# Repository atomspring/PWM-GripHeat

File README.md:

# PWM-GripHeat
Rugged PWM control for a grip heater using an attiny85 and a beefy NMOS, supporting a dual color or RGB indicator, with careful attention paid to power usage.

KiCad 8.0 Schematics and PCB files are (as expected) under the "hardware" folder, firmware is under the "firmware" folder.

Cost for a single board was TODO: fill in total costs, total including optional mechanical components was TODO:

## Hardware

The BOM (bill-of-materials) is relatively short, holding all mechanical components in [here](<hardware/bom/Mechanical BOM.md>), and the PCB components [here](<hardware/bom/BOM-PWM GripHeat-1.0.html>).

Assembly should take about an hour's work with the right tools. I use lead-free solder paste for all my work, with the PCB itself using ENIG for all pads. Soldering is sped up by using a hand-held hot air reflow gun, but all pads are big enough to facilitate hand soldering.

## Firmware
I'm using PlatformIO on VSCodium to write the fairly simple firmware, build steps:
1. Item 1
1. rr
1. te

## License
This project is:
- Software: GPL3 protected
- Hardware: CERN-OHL-S-2.0 (https://spdx.org/licenses/CERN-OHL-S-2.0.html)

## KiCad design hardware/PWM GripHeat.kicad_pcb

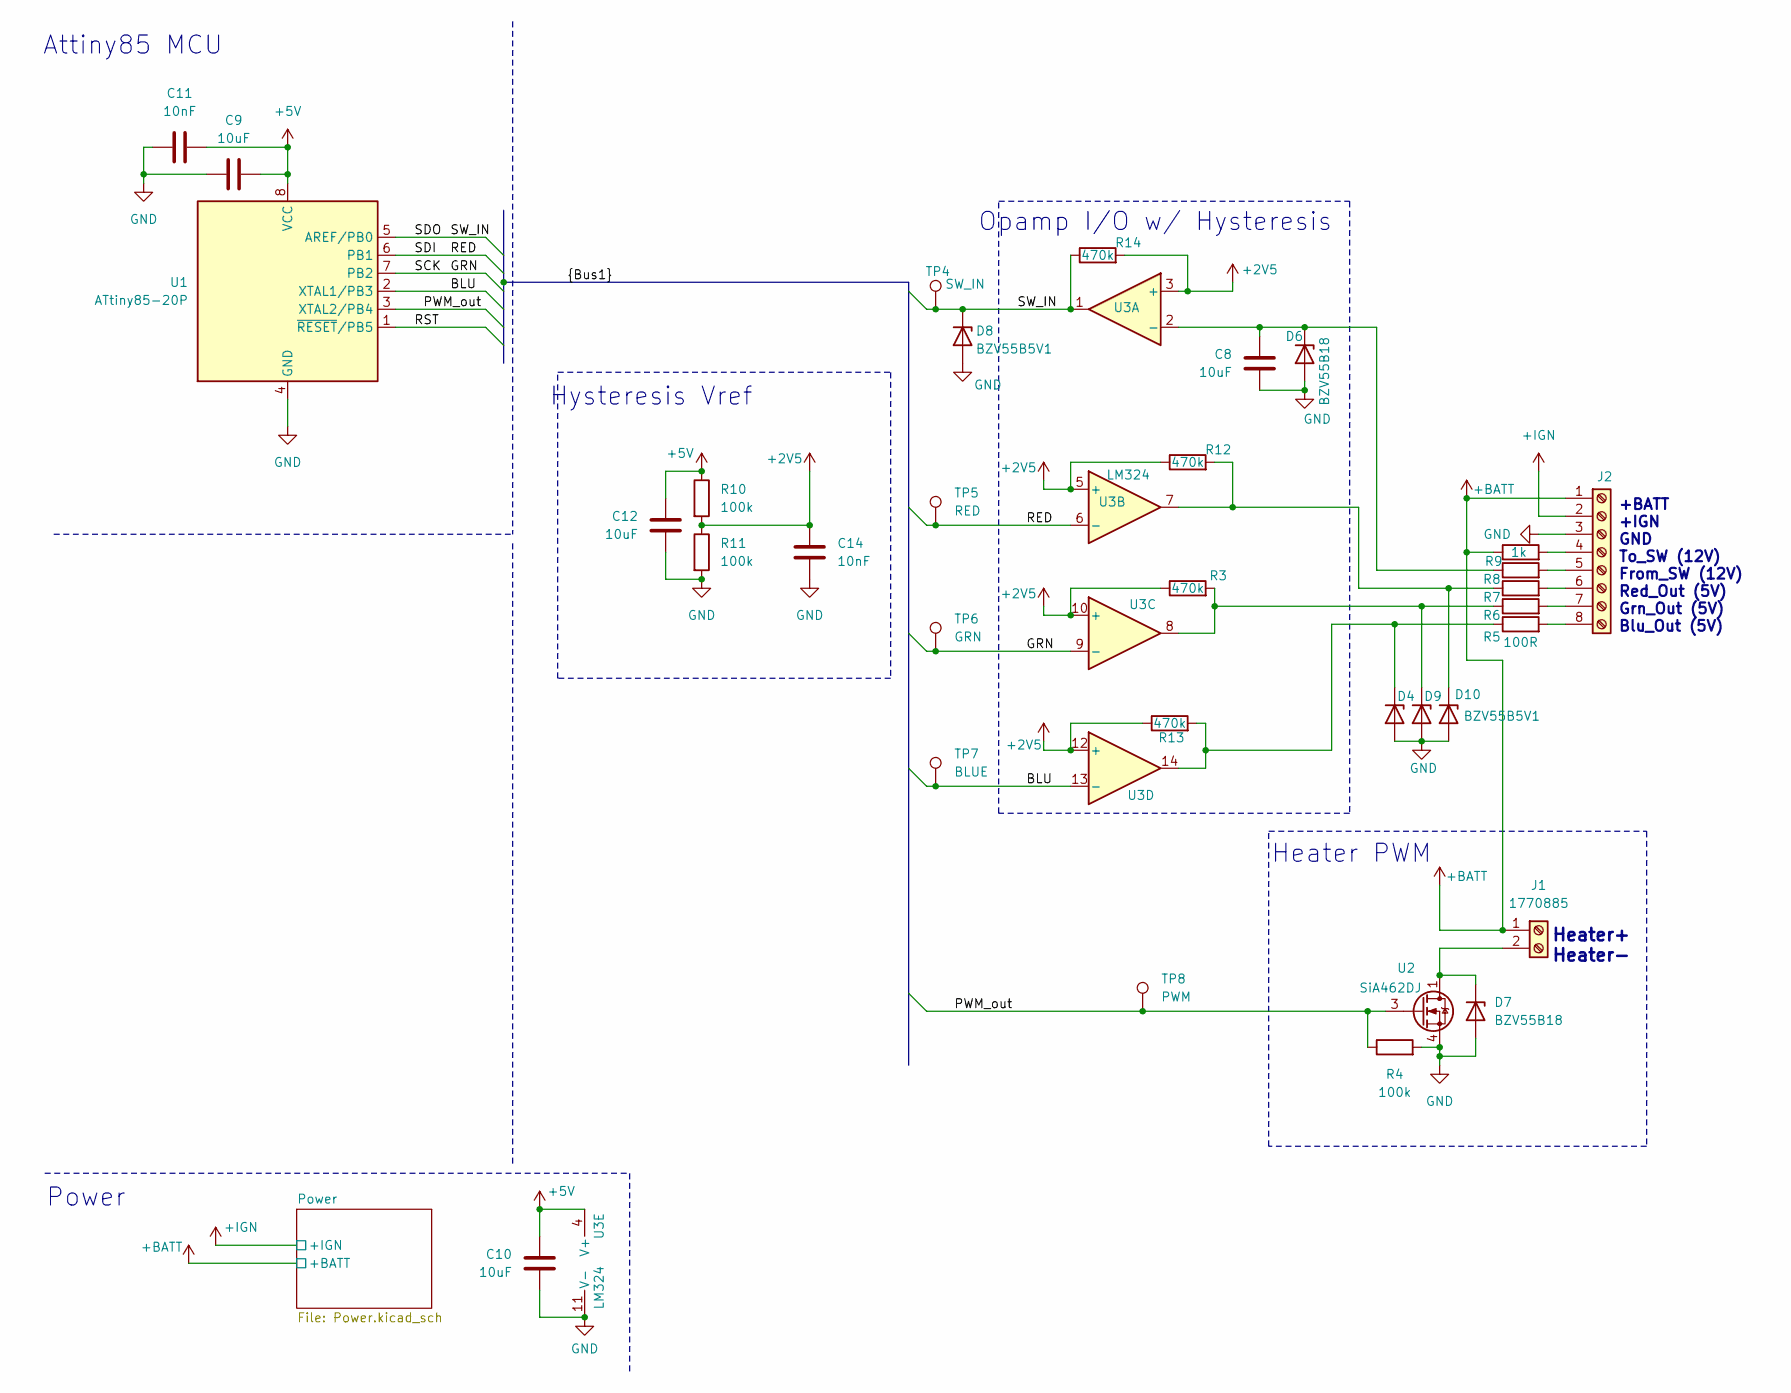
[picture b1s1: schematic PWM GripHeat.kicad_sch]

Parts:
C8, C9, C10, C12: 10uF; C_0805_2012Metric_Pad1.18x1.45mm_HandSolder; Voltage Rating 100v
C11, C14: 10nF; C_0805_2012Metric_Pad1.18x1.45mm_HandSolder
D4, D8, D9, D10: BZV55B5V1; D_MiniMELF
D6, D7: BZV55B18; D_MiniMELF
J1: 1770885; TerminalBlock_MaiXu_MX126-5.0-02P_1x02_P5.00mm
J2: Screw_Terminal_01x08; PinHeader_2x04_P2.54mm_Vertical
R3, R12, R13, R14: 470k; R_0805_2012Metric_Pad1.20x1.40mm_HandSolder
R4: 100k; R_1206_3216Metric_Pad1.30x1.75mm_HandSolder
R5, R6, R7, R8: 100R; R_0805_2012Metric_Pad1.20x1.40mm_HandSolder
R9: 1k; R_0805_2012Metric_Pad1.20x1.40mm_HandSolder
R10, R11: 100k; R_0805_2012Metric_Pad1.20x1.40mm_HandSolder
TP4: SW_IN; TestPoint_Pad_D1.5mm
TP5: RED; TestPoint_Pad_D1.5mm
TP6: GRN; TestPoint_Pad_D1.5mm
TP7: BLUE; TestPoint_Pad_D1.5mm
TP8: PWM; TestPoint_Pad_D1.5mm
U1: ATtiny85-20P; DIP-8_W7.62mm
U2: SiA462DJ; Vishay_PowerPAK_SC70-6L_Single
U3: LM324; SOIC-14_3.9x8.7mm_P1.27mm

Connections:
+2V5: C14.2, R3.1, R10.2, R11.1, R12.1, R13.1, R14.2, U3.3 (+), U3.5 (+), U3.10 (+), U3.12 (+)
+5V: C9.2, C10.2, C11.2, C12.2, R10.1, U1.8 (VCC), U3.4 (V+); also elsewhere on the board
+BATT: J1.1, J2.1, R9.1; also elsewhere on the board
+IGN: J2.2; also elsewhere on the board
/BLU: TP7.1, U1.2 (XTAL1/PB3), U3.13 (-)
/GRN: TP6.1, U1.7 (PB2), U3.9 (-)
/PWM_out: R4.1, TP8.1, U1.3 (XTAL2/PB4), U2.3 (G)
/RED: TP5.1, U1.6 (PB1), U3.6 (-)
/RST: U1.1 (~RESET/PB5)
/SDO: D8.1 (K), R14.1, TP4.1, U1.5 (AREF/PB0), U3.1
GND: C8.1, C9.1, C10.1, C11.1, C12.1, C14.1, D4.2 (A), D6.2 (A), D7.2 (A), D8.2 (A), D9.2 (A), D10.2 (A), J2.3, R4.2, R11.2, U1.4 (GND), U2.4 (S), U3.11 (V-); also elsewhere on the board
unnamed: D4.1 (K), R5.1, R13.2, U3.14
unnamed: C8.2, D6.1 (K), R8.1, U3.2 (-)
unnamed: D7.1 (K), J1.2, U2.1 (D)
unnamed: D9.1 (K), R3.2, R6.1, U3.8
unnamed: D10.1 (K), R7.1, R12.2, U3.7
unnamed: J2.4, R9.2
unnamed: J2.5, R8.2
unnamed: J2.6, R7.2
unnamed: J2.7, R6.2
unnamed: J2.8, R5.2

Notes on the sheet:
Hysteresis Vref
+BATT +IGN GND To_SW (12V) From_SW (12V) Red_Out (5V) Grn_Out (5V) Blu_Out (5V)
Heater PWM
Opamp I/O w/ Hysteresis
Heater+ Heater-
Attiny85 MCU
Power

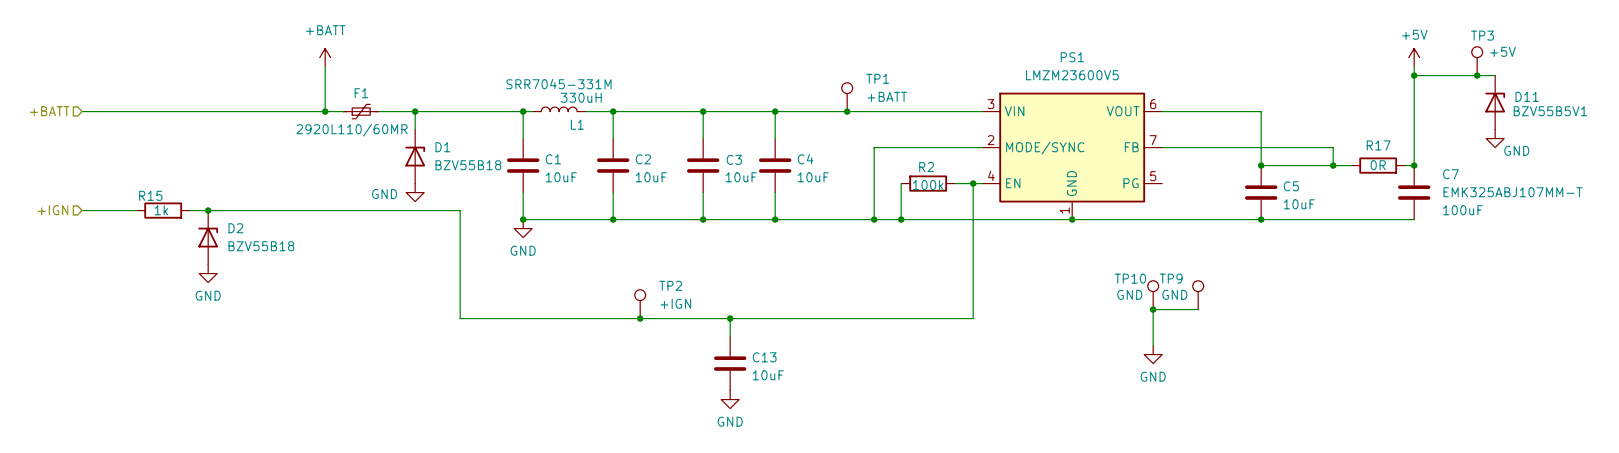
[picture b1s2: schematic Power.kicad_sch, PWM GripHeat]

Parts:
C1, C2, C3, C4, C5, C13: 10uF; C_0805_2012Metric_Pad1.18x1.45mm_HandSolder; Voltage Rating 100v
C7: EMK325ABJ107MM-T; C_1210_3225Metric_Pad1.33x2.70mm_HandSolder; Voltage Rating 16v
D1, D2: BZV55B18; D_MiniMELF
D11: BZV55B5V1; D_MiniMELF
F1: Polyfuse_Small; Fuse_2920_7451Metric_Pad2.10x5.45mm_HandSolder; MPN 2920L110/60MR
L1: 330uH; L_Bourns_SRR7045; MPN SRR7045-331M
PS1: LMZM23600V5; Texas_SIL0010A_MicroSiP-10-1EP_3.8x3mm_P0.6mm_EP0.7x2.9mm_T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
R2: 100k; R_1206_3216Metric_Pad1.30x1.75mm_HandSolder
R15: 1k; R_0805_2012Metric_Pad1.20x1.40mm_HandSolder
R17: 0R; R_0805_2012Metric_Pad1.20x1.40mm_HandSolder
TP1: +BATT; TestPoint_Pad_D1.5mm
TP2: +IGN; TestPoint_THTPad_D1.0mm_Drill0.5mm
TP3: +5V; TestPoint_Pad_D1.5mm
TP9, TP10: GND; TestPoint_THTPad_D2.0mm_Drill1.0mm

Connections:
+5V: C7.1, D11.1 (K), R17.2, TP3.1; also elsewhere on the board
+BATT: F1.1; also elsewhere on the board
+IGN: R15.1; also elsewhere on the board
GND: C1.2, C2.2, C3.2, C4.2, C5.2, C7.2, C13.2, D1.2 (A), D2.2 (A), D11.2 (A), PS1.1 (GND), PS1.2 (MODE/SYNC), PS1.11 (GND), R2.2, TP9.1, TP10.1; also elsewhere on the board
unnamed: C1.1, D1.1 (K), F1.2, L1.1
unnamed: C13.1, D2.1 (K), PS1.4 (EN), R2.1, R15.2, TP2.1
unnamed: C5.1, PS1.6 (VOUT), PS1.7 (FB), R17.1
unnamed: C2.1, C3.1, C4.1, L1.2, PS1.3 (VIN), TP1.1

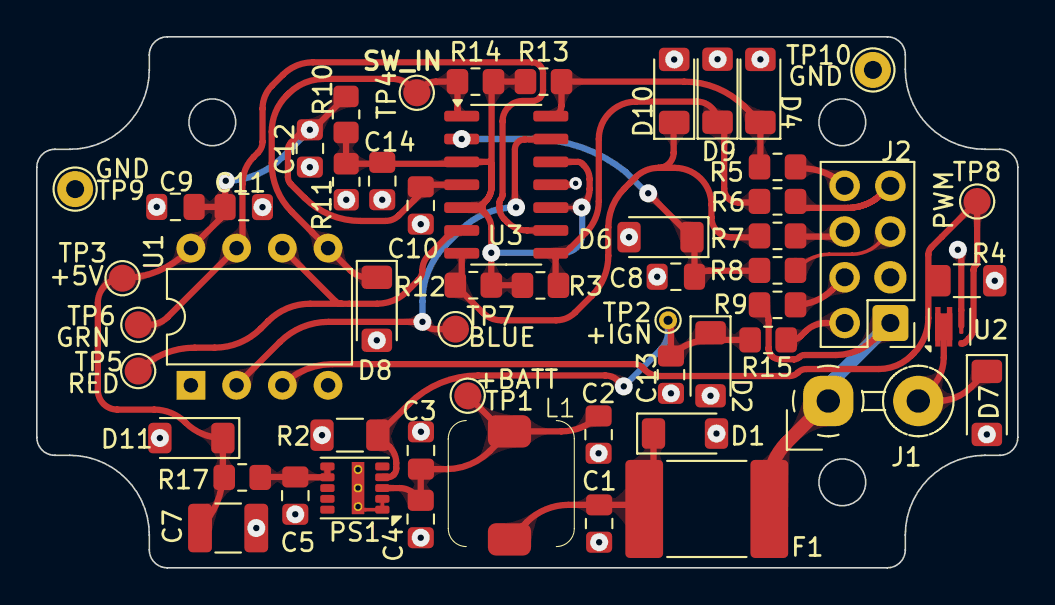
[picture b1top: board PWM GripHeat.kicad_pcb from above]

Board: 2 copper layers, 54.5 x 29.5 mm, 55 parts (0 on the bottom side), 24 nets.

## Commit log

2024-11-25 reorganizing
2024-11-28 Getting there
2024-11-28 Add power drawing
2024-12-01 PCB Basic outline
2024-12-02 Pre DRC, almost done!
2024-12-03 V1.0 release
2024-12-11 Improving documentation
2024-12-13 Adding basic firmware, further docs
2024-12-13 Released
